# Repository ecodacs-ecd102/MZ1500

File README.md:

# MZ1500
 HW and SW for MZ-1500

## MZ-1R12-18-modoki
 RAMファイルボードMZ-1R18 + バッテリーバックアップRAMボードMZ-1R12のようなもの(KiCad)

## MZ1500toDataSette
 MZ-1500のカセット端子にPET-2001のデータセッテを接続するためのアダプター(KiCad)

## ROM
 バッテリーバックアップRAMボードMZ-1R12のようなものを64KB対応するための9Z-502M-1.0Cに対する差分など
 パッチ当ては
 https://github.com/ecodacs-ecd102/MZ1200-700/tree/main/tools
 のbpatch.plなどで。

## etc
 その他いろいろ

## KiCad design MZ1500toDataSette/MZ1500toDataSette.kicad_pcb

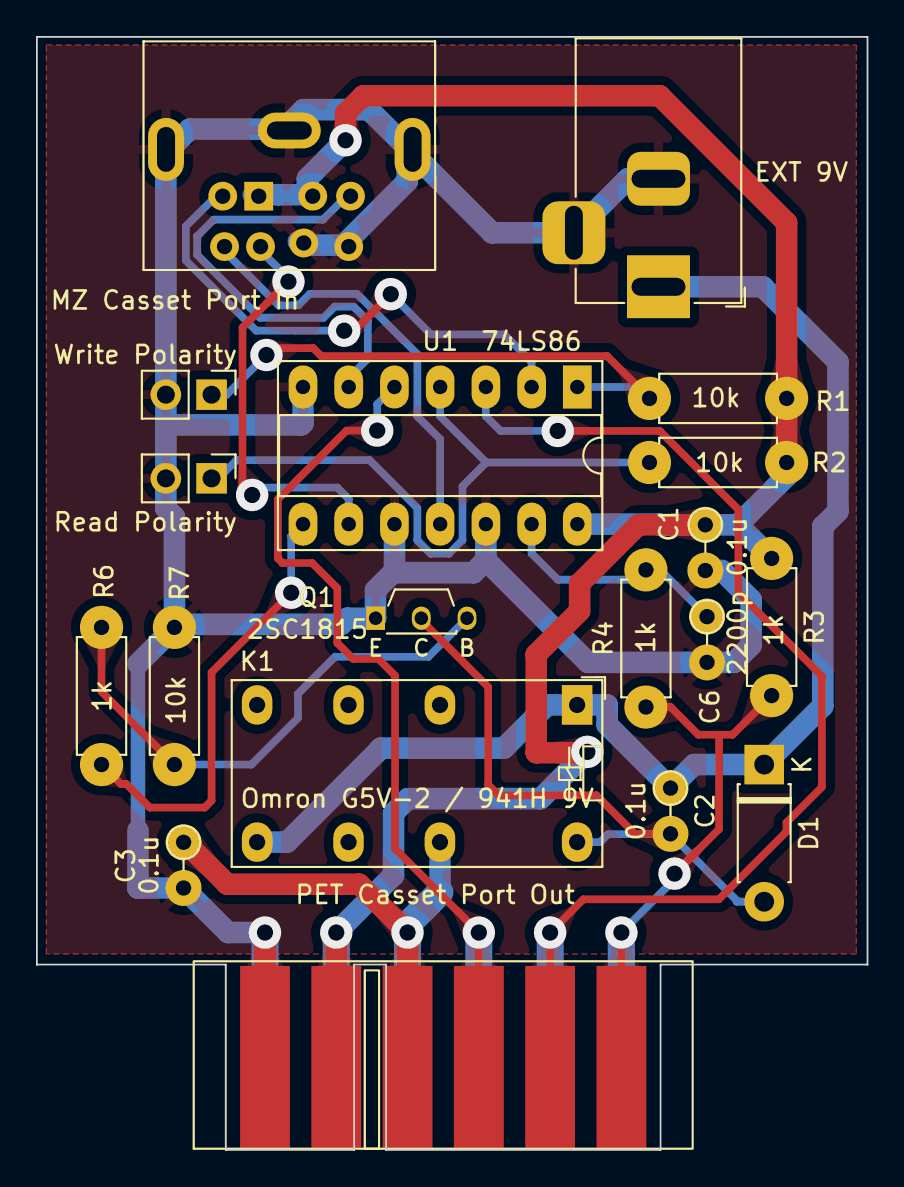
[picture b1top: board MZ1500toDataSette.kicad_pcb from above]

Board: 2 copper layers, 46.1 x 61.8 mm, 19 parts (0 on the bottom side), 17 nets.

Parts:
C1, C2, C3: 0.1u; LargePad_R_Axial_DIN0204_L3.6mm_D1.6mm_P2.54mm_Vertical
C6: 2200p; LargePad_R_Axial_DIN0204_L3.6mm_D1.6mm_P2.54mm_Vertical
D1: D_DO-41_SOD81_P7.62mm_Horizontal
J1: MZ Casset Port In; Connector_Mini-DIN_Female_8Pin_Marushin
J2: PET Casset Port Out; PET_Casset
J3: Write Polarity; PinHeader_1x02_P2.54mm_Vertical
J4: Read Polarity; PinHeader_1x02_P2.54mm_Vertical
J5: EXT 9V; BarrelJack_Horizontal
K1: Omron G5V-2 / 941H 9V; Relay_DPDT_Omron_G5V-2-LargePad
Q1: 2SC1815; TO-92S_Wide_ECB
R1, R2, R7: 10k; LargePad_R_Axial_DIN0207_L6.3mm_D2.5mm_P7.62mm_Horizontal
R3, R4, R6: 1k; LargePad_R_Axial_DIN0207_L6.3mm_D2.5mm_P7.62mm_Horizontal
U1: 74LS86; DIP-14_W7.62mm_Socket_LongPads

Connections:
+9V: C2.1, D1.1 (K), J5.1, K1.1, K1.9
/PET_MOTOR: C3.1, J2.3 (Motor), J2.C (Motor), K1.13
/PET_READ: J2.4 (Read), J2.D (Read), U1.5
/PET_SENSE: J2.6 (Sense), J2.F (Sense), R3.2, R4.1
/PET_WRITE: J2.5 (Write), J2.E (Write), U1.3
GND: C1.2, C3.2, C6.2, J1.7, J1.8, J1.9, J2.1 (GND), J2.A (GND), J3.2, J4.2, J5.2, J5.3, Q1.1 (E), R7.2, U1.7 (GND), U1.10, U1.12
MOTOR: J1.4, U1.9
unnamed: C6.1, R4.2, U1.13
unnamed: C2.2, D1.2 (A), K1.16, Q1.2 (C)
unnamed: J3.1, R1.2, U1.1
unnamed: J4.1, R2.2, U1.4
unnamed: Q1.3 (B), R6.2, R7.1
unnamed: R6.1, U1.8
READ: J1.5, U1.6
SENSE: J1.6, U1.11
VCC: C1.1, J1.1, J1.2, J2.2 (+5V), J2.B (+5V), R1.1, R2.1, R3.1, U1.14 (VCC)
WRITE: J1.3, U1.2

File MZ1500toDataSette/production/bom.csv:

Designator,Footprint,Quantity,Value,LCSC Part #
"C1, C2, C3",LargePad_R_Axial_DIN0204_L3.6mm_D1.6mm_P2.54mm_Vertical,3,0.1u,
C6,LargePad_R_Axial_DIN0204_L3.6mm_D1.6mm_P2.54mm_Vertical,1,2200p,
D1,D_DO-41_SOD81_P7.62mm_Horizontal,1,~,
J1,Connector_Mini-DIN_Female_8Pin_Marushin,1,MZ Casset Port In,
J2,PET_Casset,1,PET Casset Port Out,
J3,PinHeader_1x02_P2.54mm_Vertical,1,Write Polarity,
J4,PinHeader_1x02_P2.54mm_Vertical,1,Read Polarity,
J5,BarrelJack_Horizontal,1,EXT 9V,
K1,Relay_DPDT_Omron_G5V-2-LargePad,1,Omron G5V-2 / 941H 9V,
Q1,TO-92S_Wide_ECB,1,2SC1815,
"R1, R2, R7",LargePad_R_Axial_DIN0207_L6.3mm_D2.5mm_P7.62mm_Horizontal,3,10k,
"R3, R4, R6",LargePad_R_Axial_DIN0207_L6.3mm_D2.5mm_P7.62mm_Horizontal,3,1k,
U1,DIP-14_W7.62mm_Socket_LongPads,1,74LS86,

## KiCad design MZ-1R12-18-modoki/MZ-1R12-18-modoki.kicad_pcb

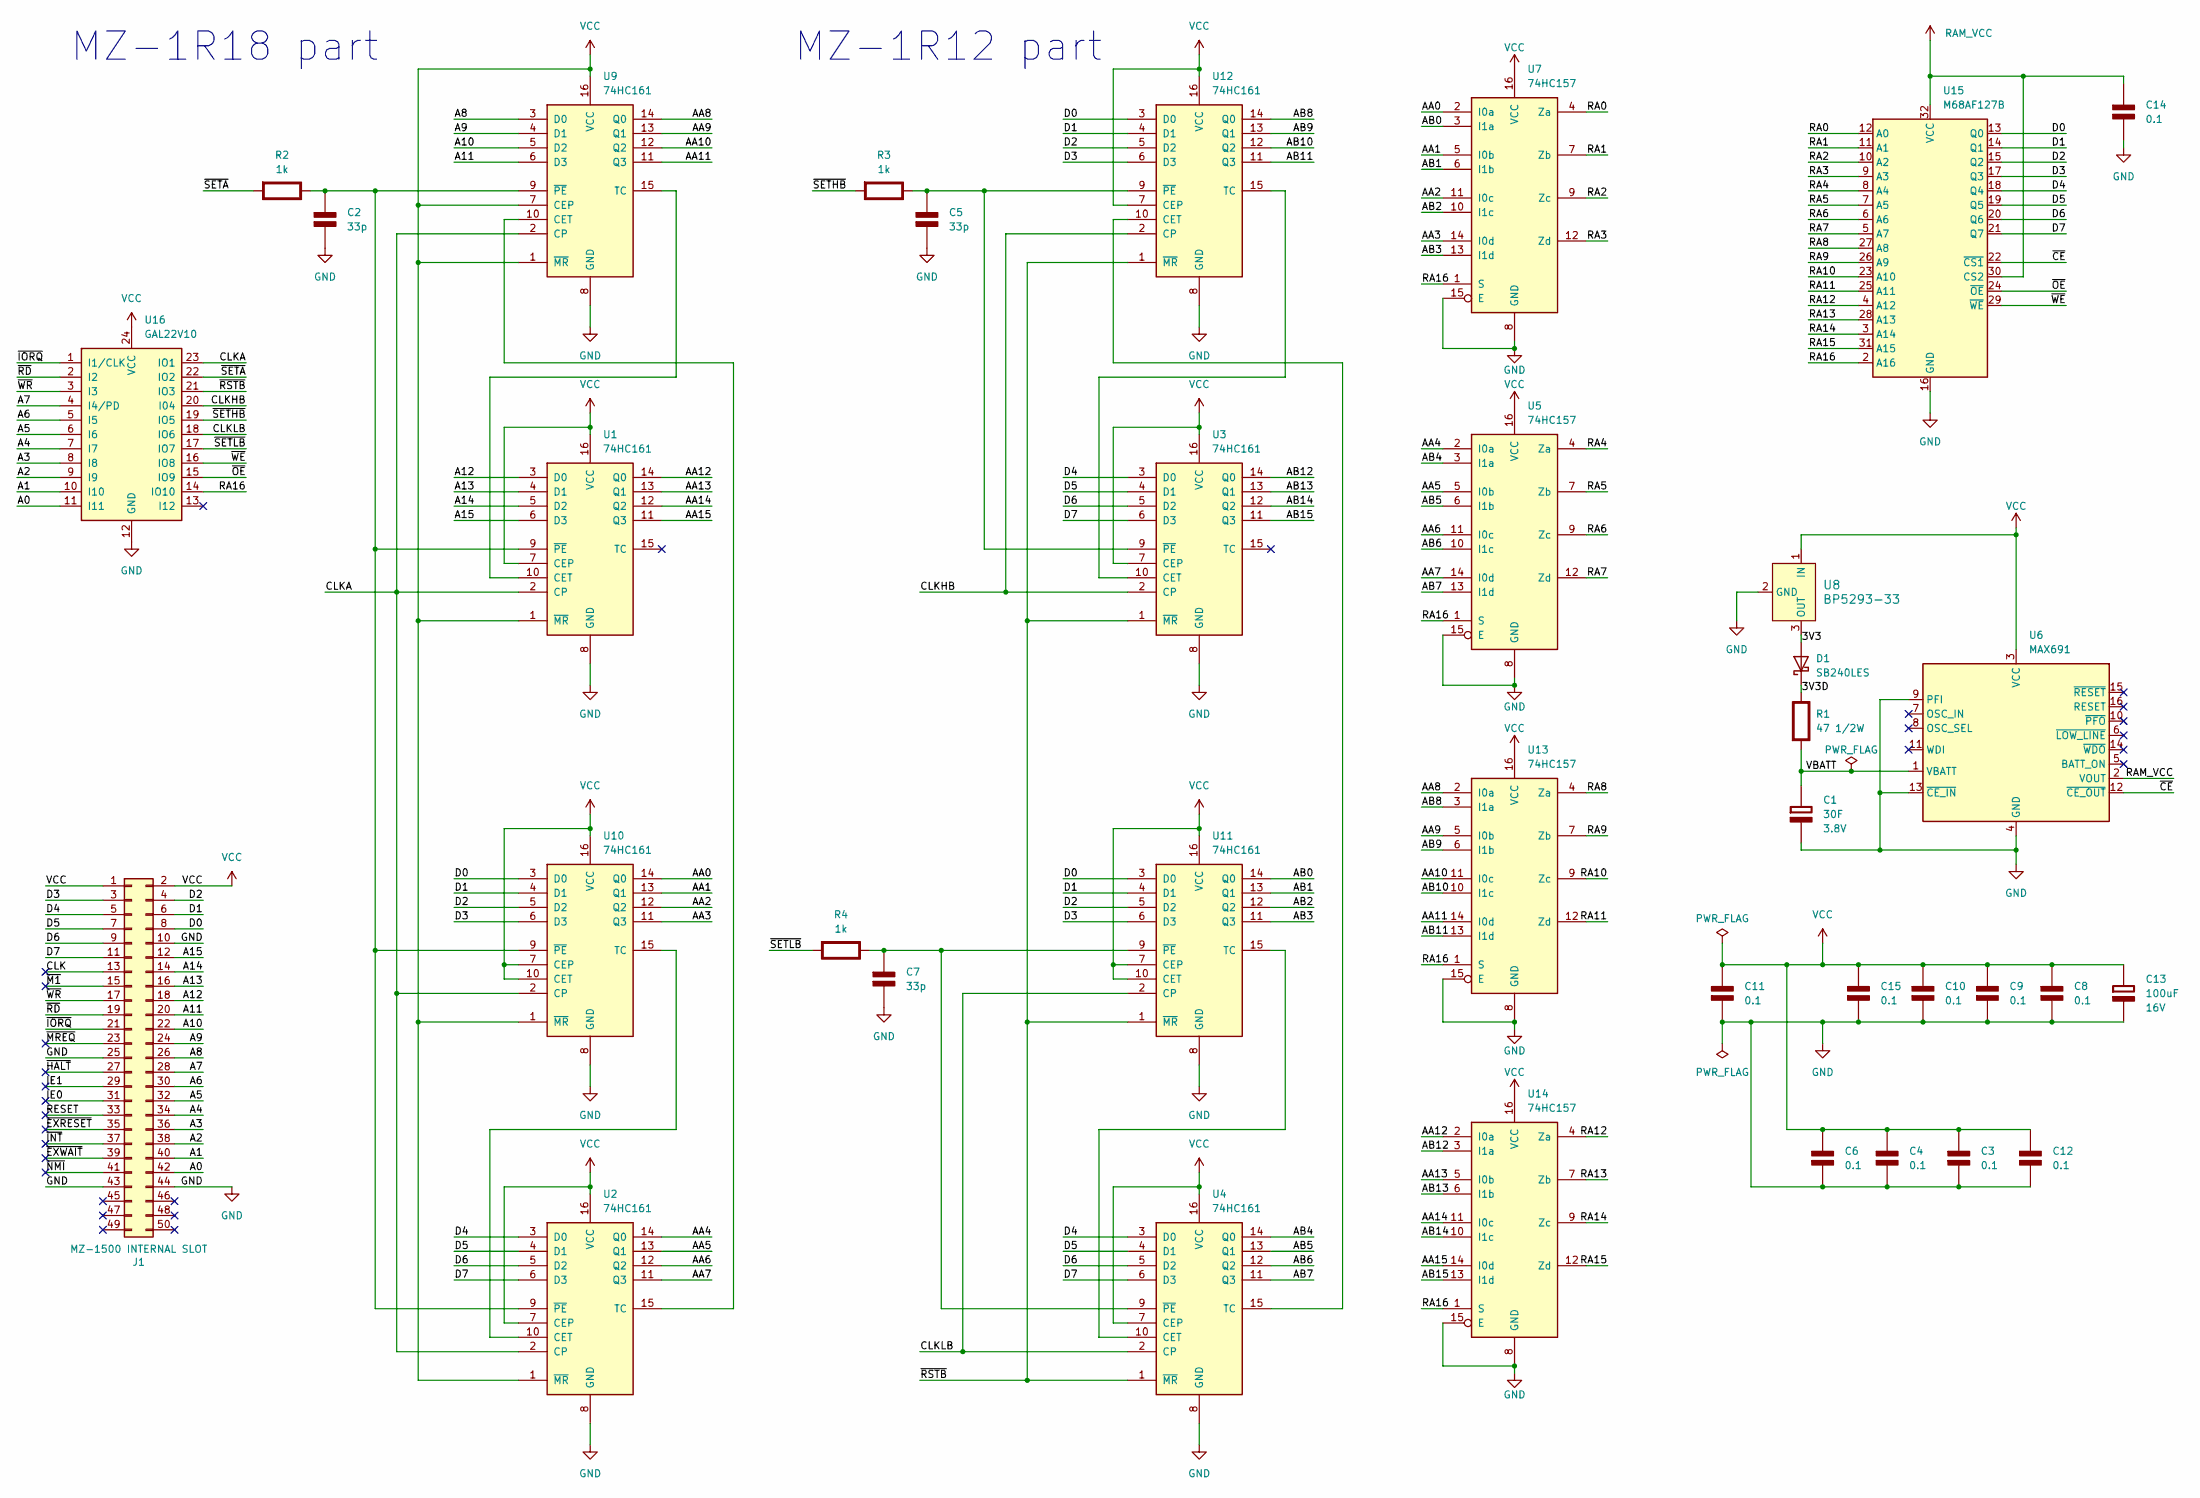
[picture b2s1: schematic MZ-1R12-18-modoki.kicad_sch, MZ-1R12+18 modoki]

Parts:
C1: 30F; CP_Radial_D8.0mm_P3.50mm; Rating 3.8V
C2, C5, C7: 33p; LargePad_R_Axial_DIN0204_L3.6mm_D1.6mm_P2.54mm_Vertical; Rating V
C3, C4, C6, C8, C9, C10, C11, C12, C14, C15: 0.1; LargePad_R_Axial_DIN0204_L3.6mm_D1.6mm_P2.54mm_Vertical; Rating V
C13: 100uF; CP_Radial_D7.5mm_P2.50mm; Rating 16V
D1: SB240LES; D_DO-41_SOD81_P10.16mm_Horizontal_CRD
J1: MZ-1500 INTERNAL SLOT; RetroPC 50Pin PCB Edge_BACK1
R1: 47 1/2W; D_A-405_P7.62mm_Horizontal_LargePad; Rating W
R2, R3, R4: 1k; LargePad_R_Axial_DIN0207_L6.3mm_D2.5mm_P7.62mm_Horizontal; Rating W
U1, U2, U3, U4, U9, U10, U11, U12: 74HC161; SOP-16_4.55x10.3mm_P1.27mm
U5, U7, U13, U14: 74HC157; SOP-16_4.55x10.3mm_P1.27mm
U6: MAX691; DIP-16_W7.62mm_Socket_LongPads
U8: BP5293-33; TO-220-3
U15: M68AF127B; SSOP-32_11.305x20.495mm_P1.27mm
U16: GAL22V10; DIP-24_W7.62mm_Socket_LongPads

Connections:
/3V3: D1.2 (A), U8.3 (OUT)
/3V3D: D1.1 (K), R1.1 (+)
/A0: J1.42, U16.11 (I11)
/A1: J1.40, U16.10 (I10)
/A2: J1.38, U16.9 (I9)
/A3: J1.36, U16.8 (I8)
/A4: J1.34, U16.7 (I7)
/A5: J1.32, U16.6 (I6)
/A6: J1.30, U16.5 (I5)
/A7: J1.28, U16.4 (I4/PD)
/A8: J1.26, U9.3 (D0)
/A9: J1.24, U9.4 (D1)
/A10: J1.22, U9.5 (D2)
/A11: J1.20, U9.6 (D3)
/A12: J1.18, U1.3 (D0)
/A13: J1.16, U1.4 (D1)
/A14: J1.14, U1.5 (D2)
/A15: J1.12, U1.6 (D3)
/AA0: U7.2 (I0a), U10.14 (Q0)
/AA1: U7.5 (I0b), U10.13 (Q1)
/AA2: U7.11 (I0c), U10.12 (Q2)
/AA3: U7.14 (I0d), U10.11 (Q3)
/AA4: U2.14 (Q0), U5.2 (I0a)
/AA5: U2.13 (Q1), U5.5 (I0b)
/AA6: U2.12 (Q2), U5.11 (I0c)
/AA7: U2.11 (Q3), U5.14 (I0d)
/AA8: U9.14 (Q0), U13.2 (I0a)
/AA9: U9.13 (Q1), U13.5 (I0b)
/AA10: U9.12 (Q2), U13.11 (I0c)
/AA11: U9.11 (Q3), U13.14 (I0d)
/AA12: U1.14 (Q0), U14.2 (I0a)
/AA13: U1.13 (Q1), U14.5 (I0b)
/AA14: U1.12 (Q2), U14.11 (I0c)
/AA15: U1.11 (Q3), U14.14 (I0d)
/AB0: U7.3 (I1a), U11.14 (Q0)
/AB1: U7.6 (I1b), U11.13 (Q1)
/AB2: U7.10 (I1c), U11.12 (Q2)
/AB3: U7.13 (I1d), U11.11 (Q3)
/AB4: U4.14 (Q0), U5.3 (I1a)
/AB5: U4.13 (Q1), U5.6 (I1b)
/AB6: U4.12 (Q2), U5.10 (I1c)
/AB7: U4.11 (Q3), U5.13 (I1d)
/AB8: U12.14 (Q0), U13.3 (I1a)
/AB9: U12.13 (Q1), U13.6 (I1b)
/AB10: U12.12 (Q2), U13.10 (I1c)
/AB11: U12.11 (Q3), U13.13 (I1d)
/AB12: U3.14 (Q0), U14.3 (I1a)
/AB13: U3.13 (Q1), U14.6 (I1b)
/AB14: U3.12 (Q2), U14.10 (I1c)
/AB15: U3.11 (Q3), U14.13 (I1d)
/CLK: J1.13
/CLKA: U1.2 (CP), U2.2 (CP), U9.2 (CP), U10.2 (CP), U16.23 (IO1)
/CLKHB: U3.2 (CP), U12.2 (CP), U16.20 (I04)
/CLKLB: U4.2 (CP), U11.2 (CP), U16.18 (IO6)
/D0: J1.8, U10.3 (D0), U11.3 (D0), U12.3 (D0), U15.13 (Q0)
/D1: J1.6, U10.4 (D1), U11.4 (D1), U12.4 (D1), U15.14 (Q1)
/D2: J1.4, U10.5 (D2), U11.5 (D2), U12.5 (D2), U15.15 (Q2)
/D3: J1.3, U10.6 (D3), U11.6 (D3), U12.6 (D3), U15.17 (Q3)
/D4: J1.5, U2.3 (D0), U3.3 (D0), U4.3 (D0), U15.18 (Q4)
/D5: J1.7, U2.4 (D1), U3.4 (D1), U4.4 (D1), U15.19 (Q5)
/D6: J1.9, U2.5 (D2), U3.5 (D2), U4.5 (D2), U15.20 (Q6)
/D7: J1.11, U2.6 (D3), U3.6 (D3), U4.6 (D3), U15.21 (Q7)
/IE0: J1.31
/IE1: J1.29
/RA0: U7.4 (Za), U15.12 (A0)
/RA1: U7.7 (Zb), U15.11 (A1)
/RA2: U7.9 (Zc), U15.10 (A2)
/RA3: U7.12 (Zd), U15.9 (A3)
/RA4: U5.4 (Za), U15.8 (A4)
/RA5: U5.7 (Zb), U15.7 (A5)
/RA6: U5.9 (Zc), U15.6 (A6)
/RA7: U5.12 (Zd), U15.5 (A7)
/RA8: U13.4 (Za), U15.27 (A8)
/RA9: U13.7 (Zb), U15.26 (A9)
/RA10: U13.9 (Zc), U15.23 (A10)
/RA11: U13.12 (Zd), U15.25 (A11)
/RA12: U14.4 (Za), U15.4 (A12)
/RA13: U14.7 (Zb), U15.28 (A13)
/RA14: U14.9 (Zc), U15.3 (A14)
/RA15: U14.12 (Zd), U15.31 (A15)
/RA16: U5.1 (S), U7.1 (S), U13.1 (S), U14.1 (S), U15.2 (A16), U16.14 (IO10)
/RESET: J1.33
/VBATT: C1.1 (+), R1.2 (-), U6.1 (VBATT)
/~CE: U6.12 (~CE_OUT), U15.22 (~CS1)
/~EXRESET: J1.35
/~EXWAIT: J1.39
/~HALT: J1.27
/~INT: J1.37
/~IORQ: J1.21, U16.1 (I1/CLK)
/~M1: J1.15
/~MREQ: J1.23
/~NMI: J1.41
/~OE: U15.24 (~OE), U16.15 (IO9)
/~RD: J1.19, U16.2 (I2)
/~RSTB: U3.1 (~MR), U4.1 (~MR), U11.1 (~MR), U12.1 (~MR), U16.21 (IO3)
/~SETA: R2.2 (-), U16.22 (IO2)
/~SETHB: R3.2 (-), U16.19 (IO5)
/~SETLB: R4.2 (-), U16.17 (IO7)
/~WE: U15.29 (~WE), U16.16 (IO8)
/~WR: J1.17, U16.3 (I3)
GND: C1.2 (-), C2.2 (-), C3.2 (-), C4.2 (-), C5.2 (-), C6.2 (-), C7.2 (-), C8.2 (-), C9.2 (-), C10.2 (-), C11.2 (-), C12.2 (-), C13.2 (-), C14.2 (-), C15.2 (-), J1.10, J1.25, J1.43, J1.44, U1.8 (GND), U2.8 (GND), U3.8 (GND), U4.8 (GND), U5.8 (GND), U5.15 (E), U6.4 (GND), U6.9 (PFI), U6.13 (~CE_IN), U7.8 (GND), U7.15 (E), U8.2 (GND), U9.8 (GND), U10.8 (GND), U11.8 (GND), U12.8 (GND), U13.8 (GND), U13.15 (E), U14.8 (GND), U14.15 (E), U15.16 (GND), U16.12 (GND)
unnamed: C2.1 (+), R2.1 (+), U1.9 (~PE), U2.9 (~PE), U9.9 (~PE), U10.9 (~PE)
unnamed: C5.1 (+), R3.1 (+), U3.9 (~PE), U12.9 (~PE)
unnamed: C7.1 (+), R4.1 (+), U4.9 (~PE), U11.9 (~PE)
unnamed: U1.10 (CET), U9.15 (TC)
unnamed: U2.15 (TC), U9.10 (CET)
unnamed: U2.10 (CET), U10.15 (TC)
unnamed: U4.10 (CET), U11.15 (TC)
unnamed: U4.15 (TC), U12.10 (CET)
unnamed: U3.10 (CET), U12.15 (TC)
RAM_VCC: C14.1 (+), U6.2 (VOUT), U15.30 (CS2), U15.32 (VCC)
VCC: C3.1 (+), C4.1 (+), C6.1 (+), C8.1 (+), C9.1 (+), C10.1 (+), C11.1 (+), C12.1 (+), C13.1 (+), C15.1 (+), J1.1, J1.2, U1.1 (~MR), U1.7 (CEP), U1.16 (VCC), U2.1 (~MR), U2.7 (CEP), U2.16 (VCC), U3.7 (CEP), U3.16 (VCC), U4.7 (CEP), U4.16 (VCC), U5.16 (VCC), U6.3 (VCC), U7.16 (VCC), U8.1 (IN), U9.1 (~MR), U9.7 (CEP), U9.16 (VCC), U10.1 (~MR), U10.7 (CEP), U10.10 (CET), U10.16 (VCC), U11.7 (CEP), U11.10 (CET), U11.16 (VCC), U12.7 (CEP), U12.16 (VCC), U13.16 (VCC), U14.16 (VCC), U16.24 (VCC)

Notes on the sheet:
MZ-1R18 part
MZ-1R12 part

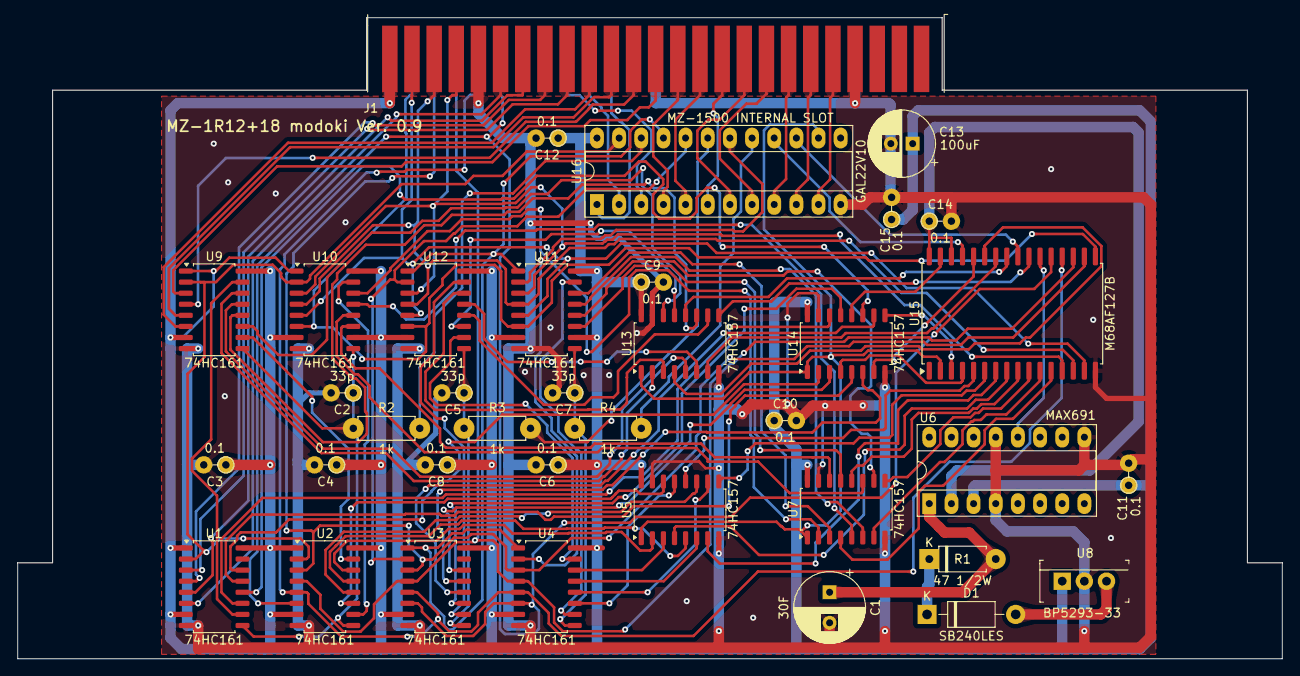
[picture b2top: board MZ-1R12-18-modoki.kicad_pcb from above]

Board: 2 copper layers, 145.0 x 73.5 mm, 37 parts (0 on the bottom side), 101 nets.

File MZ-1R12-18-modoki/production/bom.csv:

Designator,Footprint,Quantity,Value,LCSC Part #
C1,CP_Radial_D8.0mm_P3.50mm,1,30F,
"C10, C11, C12, C14, C15, C3, C4, C6, C8, C9",LargePad_R_Axial_DIN0204_L3.6mm_D1.6mm_P2.54mm_Vertical,10,0.1,
C13,CP_Radial_D7.5mm_P2.50mm,1,100uF,
"C2, C5, C7",LargePad_R_Axial_DIN0204_L3.6mm_D1.6mm_P2.54mm_Vertical,3,33p,
D1,D_DO-41_SOD81_P10.16mm_Horizontal_CRD,1,SB240LES,
J1,RetroPC 50Pin PCB Edge_BACK1,1,MZ-1500 INTERNAL SLOT,
R1,D_A-405_P7.62mm_Horizontal_LargePad,1,47 1/2W,
"R2, R3, R4",LargePad_R_Axial_DIN0207_L6.3mm_D2.5mm_P7.62mm_Horizontal,3,1k,
"U1, U10, U11, U12, U2, U3, U4, U9",SOP-16_4.55x10.3mm_P1.27mm,8,74HC161,
"U13, U14, U5, U7",SOP-16_4.55x10.3mm_P1.27mm,4,74HC157,
U15,SSOP-32_11.305x20.495mm_P1.27mm,1,M68AF127B,
U16,DIP-24_W7.62mm_Socket_LongPads,1,GAL22V10,
U6,DIP-16_W7.62mm_Socket_LongPads,1,MAX691,
U8,TO-220-3,1,BP5293-33,

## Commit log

2024-12-29 1st release
    For C105
2024-12-29 etcを追加
    etcを追加
2024-12-29 EC EQコマンド追加パッチ
    EC EQコマンドを追加するパッチを追加。
    QDからSRAMに書けるようになります。
2024-12-30 Create EQ_CMD.ASM
    EQ, ECコマンドパッチ試作
2024-12-31 ECコマンド改善
    チェックサムエラーが出ないようにした。
2024-12-31 Update MZ1500.txt
    RGB2HDMIのパラメータをより追い込んだ
